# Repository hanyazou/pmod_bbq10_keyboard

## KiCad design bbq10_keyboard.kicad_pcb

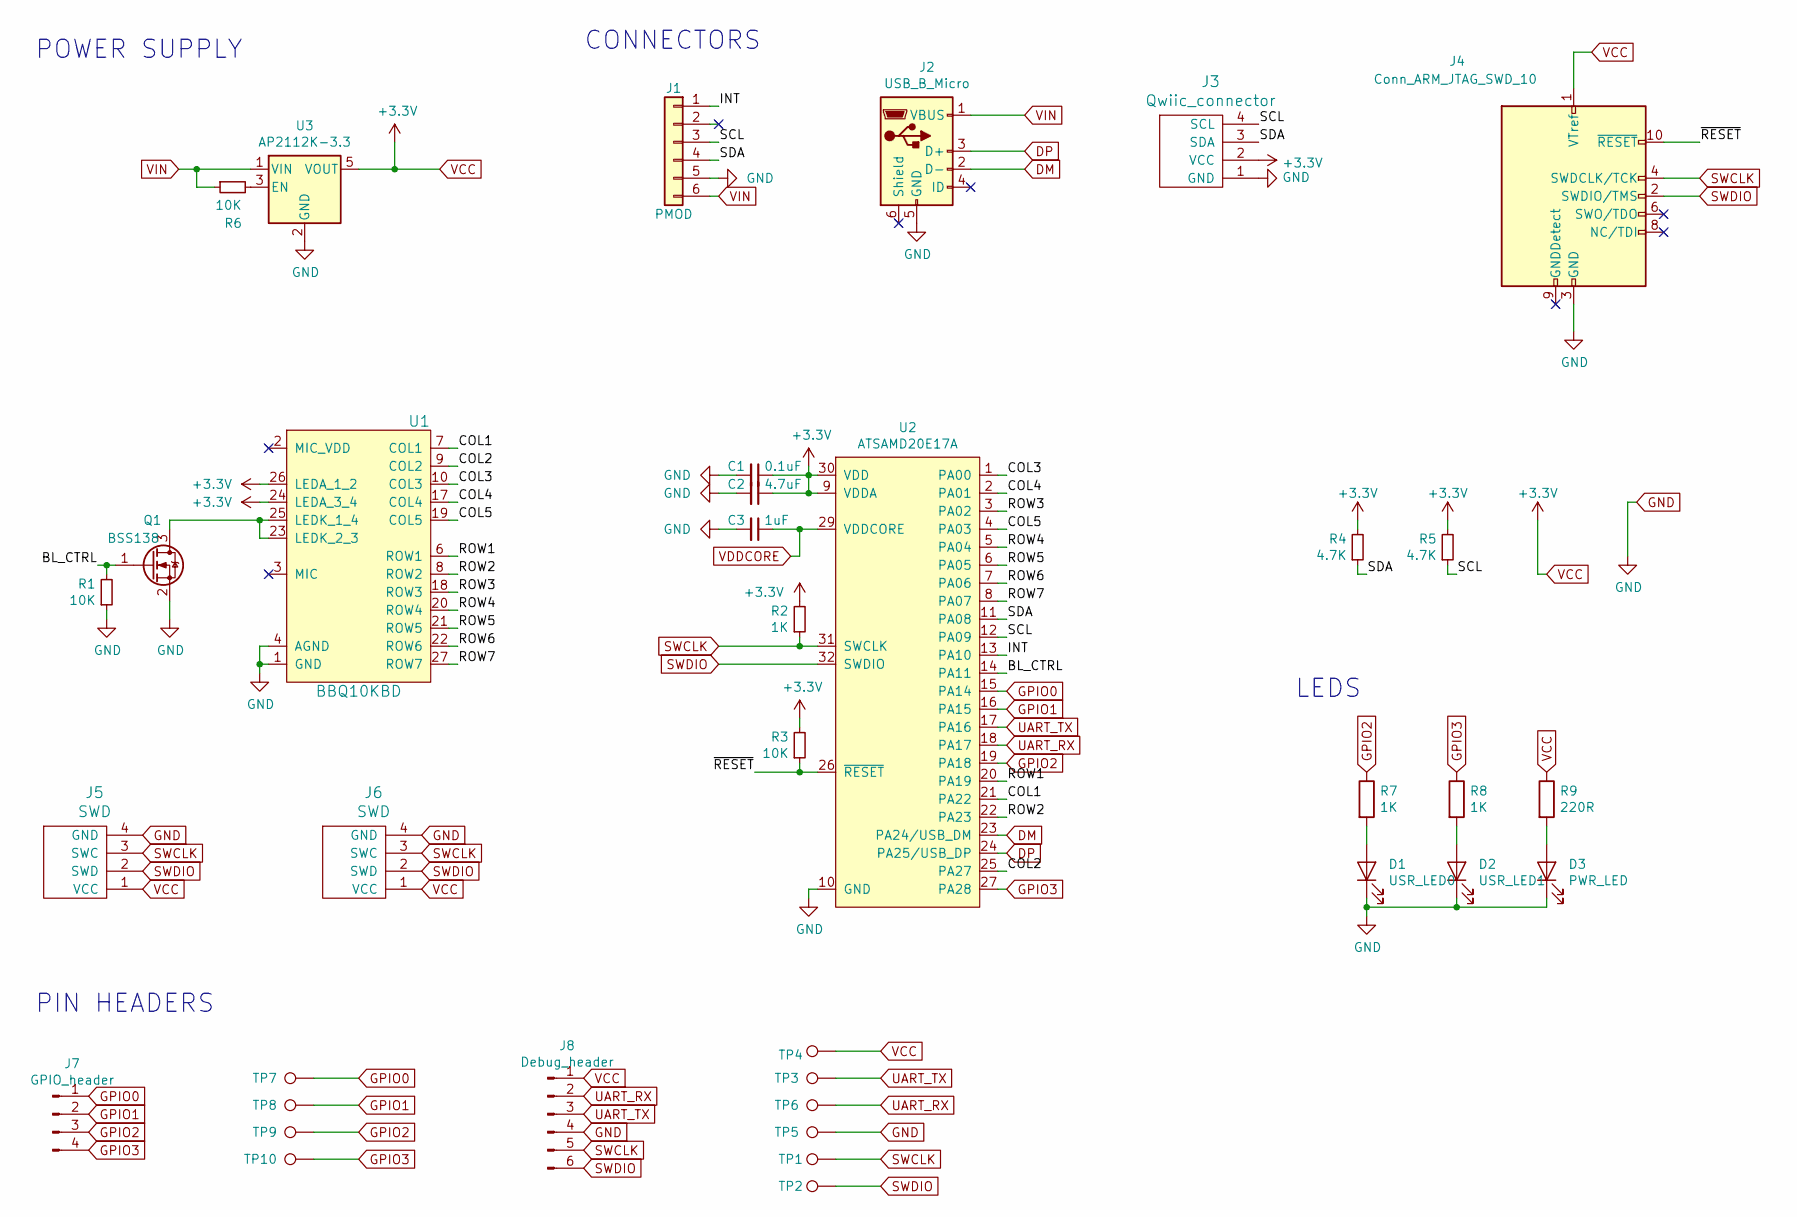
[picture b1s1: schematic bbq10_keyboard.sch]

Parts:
C1: 0.1uF; C_0603_1608Metric
C2: 4.7uF; C_0603_1608Metric
C3: 1uF; C_0603_1608Metric
D1: USR_LED0; LED_0603_1608Metric_Pad1.05x0.95mm_HandSolder
D2: USR_LED1; LED_0603_1608Metric_Pad1.05x0.95mm_HandSolder
D3: PWR_LED; LED_0603_1608Metric_Pad1.05x0.95mm_HandSolder
J1: PMOD; PMODPinHeader_1x06_P2.54mm_Horizontal
J2: USB_B_Micro; USB_Micro-B_Molex_47346-0001
J3: Qwiic_connector; JST_SH_SM04B-SRSS-TB_1x04-1MP_P1.00mm_Horizontal
J4: Conn_ARM_JTAG_SWD_10; PinHeader_2x05_P1.27mm_Vertical_SMD
J5: SWD; Conn4 1.0mm pitch
J6: SWD; PinHeader_1x04_P2.54mm_Vertical_SMD_Pin1Left
J7: GPIO_header; PinHeader_1x04_P2.54mm_Vertical_SMD_Pin1Left
J8: Debug_header; PinHeader_1x06_P2.54mm_Vertical_SMD_Pin1Left
Q1: BSS138; SOT-23
R1, R3, R6: 10K; R_0603_1608Metric_Pad1.05x0.95mm_HandSolder
R2, R7, R8: 1K; R_0603_1608Metric_Pad1.05x0.95mm_HandSolder
R4, R5: 4.7K; R_0603_1608Metric_Pad1.05x0.95mm_HandSolder
R9: 220R; R_0603_1608Metric_Pad1.05x0.95mm_HandSolder
TP1: TP_SWCLK; TestPoint_Pad_D1.0mm
TP2: TP_SWDIO; TestPoint_Pad_D1.0mm
TP3: TP_UART_TX; TestPoint_Pad_D1.0mm
TP4: TP_VCC; TestPoint_Pad_D1.0mm
TP5: TP_GND; TestPoint_Pad_D1.0mm
TP6: TP_UART_RX; TestPoint_Pad_D1.0mm
TP7: TP_GPIO0; TestPoint_Pad_D1.0mm
TP8: TP_GPIO1; TestPoint_Pad_D1.0mm
TP9: TP_GPIO2; TestPoint_Pad_D1.0mm
TP10: TP_GPIO3; TestPoint_Pad_D1.0mm
U1: BBQ10KBD; BM14B(0.8)-24DS-0.4V(53)
U2: ATSAMD20E17A; TQFP-32_7x7mm_P0.8mm
U3: AP2112K-3.3; SOT-23-5

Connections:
/BL_CTRL: Q1.1 (G), R1.2, U2.14 (PA11)
/COL1: U1.7 (COL1), U2.21 (PA22)
/COL2: U1.9 (COL2), U2.25 (PA27)
/COL3: U1.10 (COL3), U2.1 (PA00)
/COL4: U1.17 (COL4), U2.2 (PA01)
/COL5: U1.19 (COL5), U2.4 (PA03)
/INT: J1.1, U2.13 (PA10)
/ROW1: U1.6 (ROW1), U2.20 (PA19)
/ROW2: U1.8 (ROW2), U2.22 (PA23)
/ROW3: U1.18 (ROW3), U2.3 (PA02)
/ROW4: U1.20 (ROW4), U2.5 (PA04)
/ROW5: U1.21 (ROW5), U2.6 (PA05)
/ROW6: U1.22 (ROW6), U2.7 (PA06)
/ROW7: U1.27 (ROW7), U2.8 (PA07)
/SCL: J1.3, J3.4 (SCL), R5.1, U2.12 (PA09)
/SDA: J1.4, J3.3 (SDA), R4.1, U2.11 (PA08)
/~RESET~: J4.10 (~RESET~), R3.1, U2.26 (~RESET~)
DM: J2.2 (D-), U2.23 (PA24/USB_DM)
DP: J2.3 (D+), U2.24 (PA25/USB_DP)
GND: C1.2, C2.2, C3.2, D1.1 (K), D2.1 (K), D3.1 (K), J1.5, J2.5 (GND), J3.1 (GND), J4.3 (GND), J4.5 (GND), J5.4 (GND), J6.4 (GND), J8.4, Q1.2 (S), R1.1, TP5.1, U1.1 (GND), U1.4 (AGND), U1.5 (GND), U1.11 (GND), U1.12 (GND), U1.13 (GND), U1.14 (GND), U1.15 (GND), U1.16 (GND), U1.28 (GND), U2.10 (GND), U2.28 (GND), U3.2 (GND)
GPIO0: J7.1, TP7.1, U2.15 (PA14)
GPIO1: J7.2, TP8.1, U2.16 (PA15)
GPIO2: J7.3, R7.1, TP9.1, U2.19 (PA18)
GPIO3: J7.4, R8.1, TP10.1, U2.27 (PA28)
unnamed: D1.2 (A), R7.2
unnamed: D2.2 (A), R8.2
unnamed: D3.2 (A), R9.2
unnamed: Q1.3 (D), U1.23 (LEDK_2_3), U1.25 (LEDK_1_4)
unnamed: R6.2, U3.3 (EN)
SWCLK: J4.4 (SWDCLK/TCK), J5.3 (SWC), J6.3 (SWC), J8.5, R2.1, TP1.1, U2.31 (SWCLK)
SWDIO: J4.2 (SWDIO/TMS), J5.2 (SWD), J6.2 (SWD), J8.6, TP2.1, U2.32 (SWDIO)
UART_RX: J8.2, TP6.1, U2.18 (PA17)
UART_TX: J8.3, TP3.1, U2.17 (PA16)
VCC: C1.1, C2.1, J3.2 (VCC), J4.1 (VTref), J5.1 (VCC), J6.1 (VCC), J8.1, R2.2, R3.2, R4.2, R5.2, R9.1, TP4.1, U1.24 (LEDA_3_4), U1.26 (LEDA_1_2), U2.9 (VDDA), U2.30 (VDD), U3.5 (VOUT)
VDDCORE: C3.1, U2.29 (VDDCORE)
VIN: J1.6, J2.1 (VBUS), R6.1, U3.1 (VIN)

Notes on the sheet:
PIN HEADERS
POWER SUPPLY
CONNECTORS
LEDS

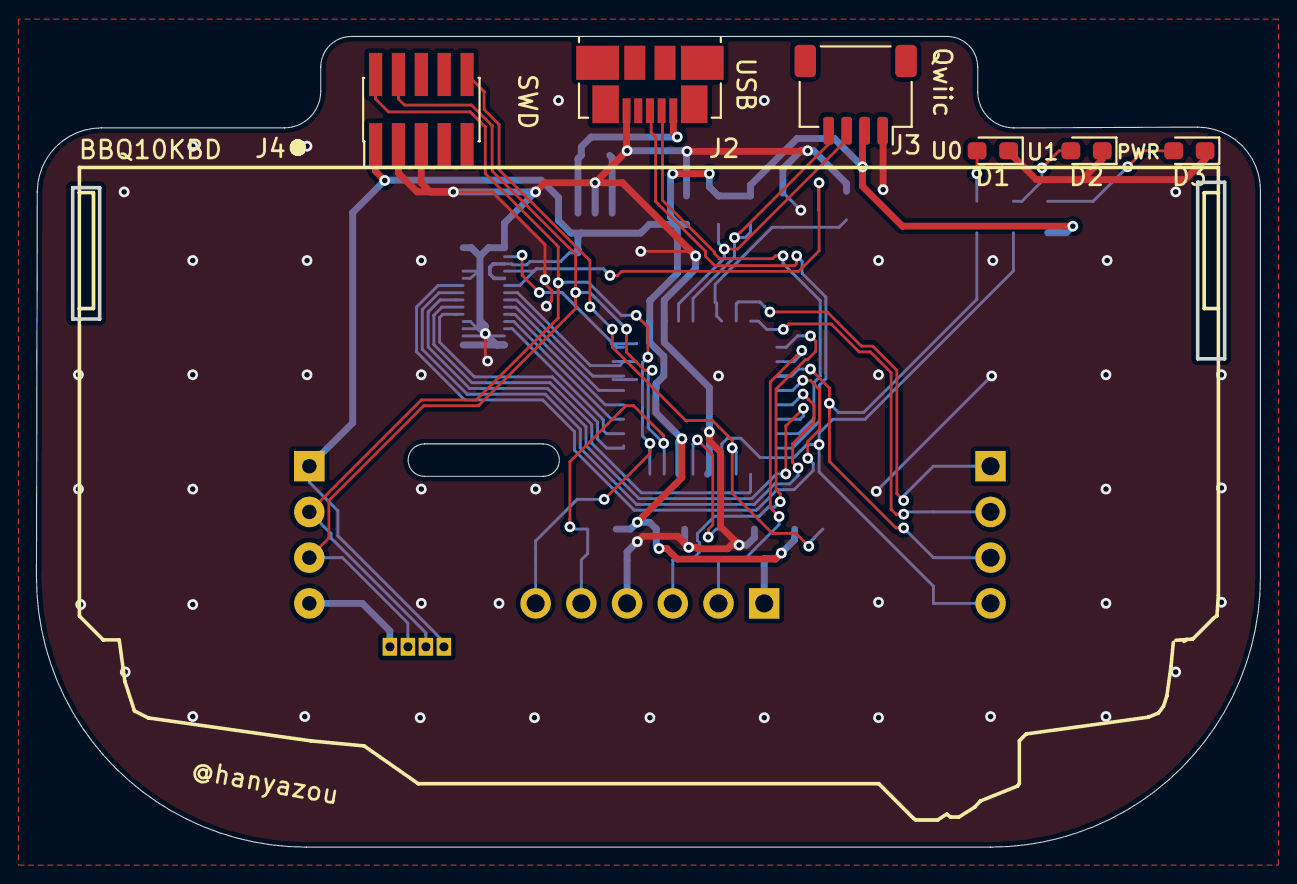
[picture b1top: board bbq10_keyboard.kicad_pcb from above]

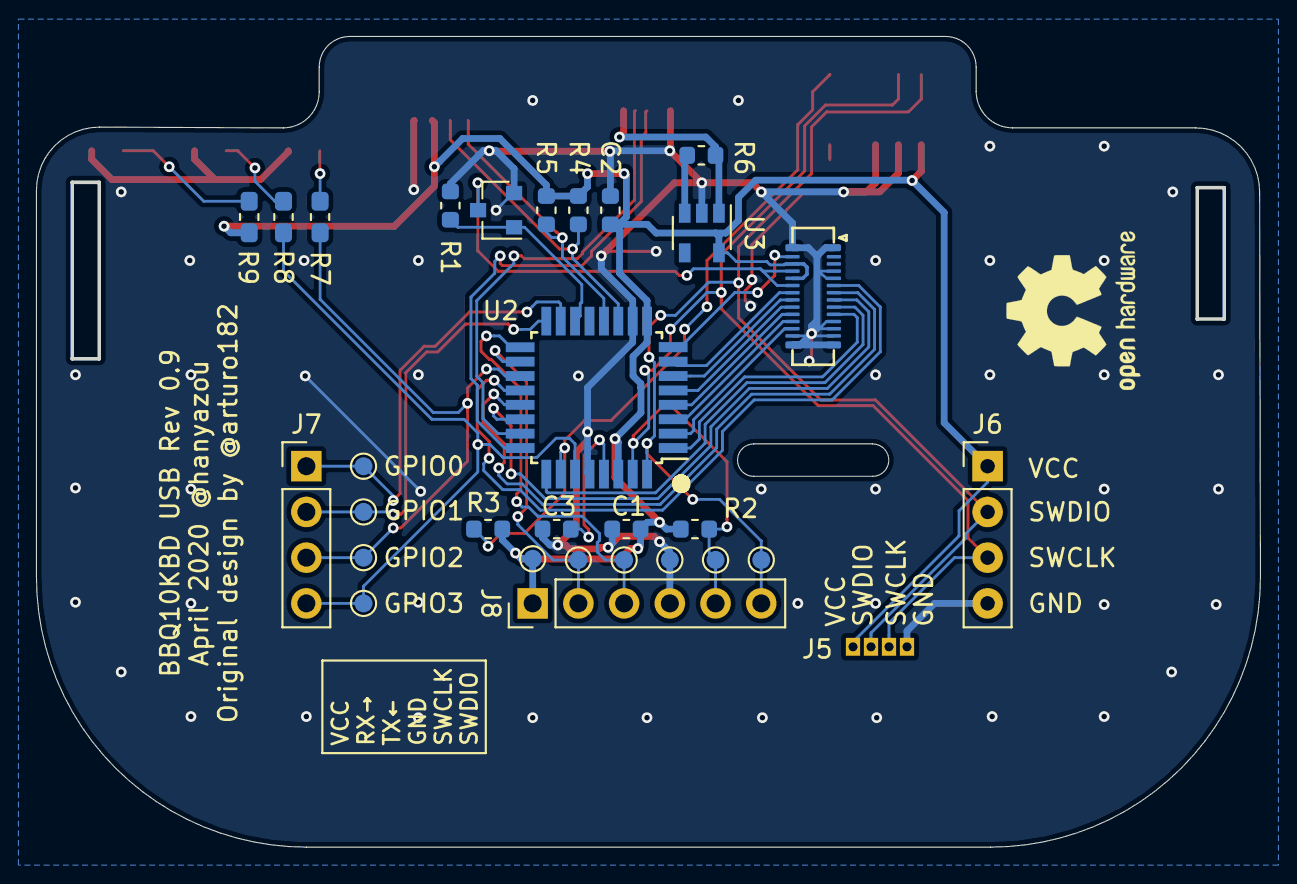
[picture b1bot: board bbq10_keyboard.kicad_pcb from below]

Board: 2 copper layers, 68.0 x 45.0 mm, 36 parts (29 on the bottom side), 35 nets.

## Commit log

2020-03-22 USB BBQ10 keyboard rev 0.5
2020-04-12 USB BBQ10 keyboard rev 0.9
